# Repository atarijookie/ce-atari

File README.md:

# CosmosEx?
An ACSI/SCSI storage device connecting Raspberry Pi to the Atari 16/32 Bit range of computers
# What's what

ce_conf - Atari configuration client

ce_dd_bootsectors	- ACSI/SCSI boot sectors

ce_dd_prg	- driver for translated/network drives, date setting and screenshots

ce_fdd_prg	- Atari floppy emulator configuration client

ce_fdd_ttp	- Atari floppy emulator image mount helper

ce_franz_fw	- Firmware for floppy emulator

ce_hans_fw	- Firmware for harddisk emulator

ce_hdimg_ttp - Atari disk image mounter

ce_main_app	- Pi main app (translated/network drives, Webserver, HTTP Rest(like) API)

ce_mount_acc	- Atari unmount helper as ACC

ce_mount_prg	- Atari unmount helper

ce_screencast	- Atari screencast driver

cosmosex_downloader	- Atari ce_dd copier

cosmosex_fakesting	- Atari network driver (WIP)

cosmosex_onpc_pasti	- PC pasti.dll connection layer to PC compile ce_main_app

ffmpeg_build - build ffmpeg binary on RPi

flash_stm32	- Pi helper to flash STM32

flash_xilinx	- Pi helper to flash Xilinx

test_acsi	- Atari ACSI/SCSI transfer tester

test_filesystem	- Atari filesystem tester

test_floppy	- Atari floppy emulation tester

test_floppy_read	- Atari another floppy emulation tester

test_manual	- Atari another ACSI transfer tester

test_sting	- Atari STiNG tester

update - build the CosmosEx .zip update package

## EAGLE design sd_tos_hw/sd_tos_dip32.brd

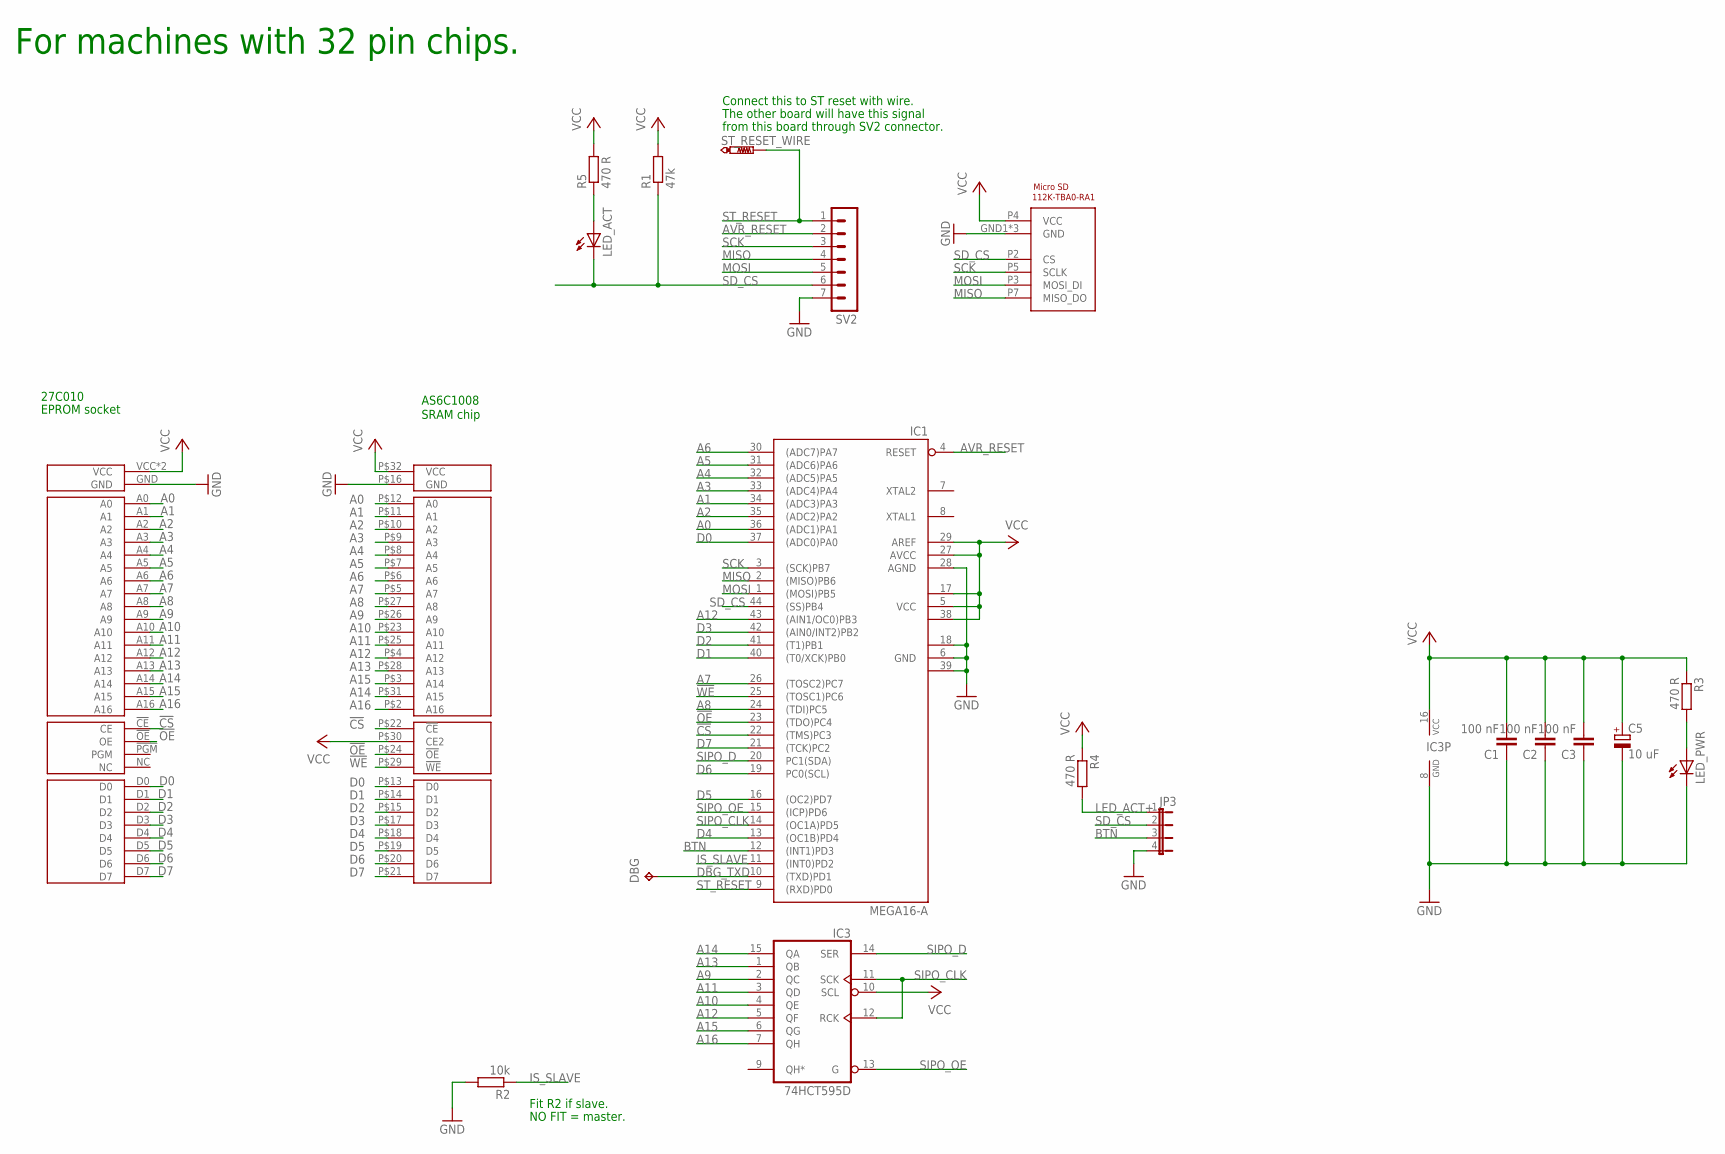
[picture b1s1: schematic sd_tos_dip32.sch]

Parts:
C1, C2, C3: 100 nF; C0603
C5: 10 uF; SANYO-OSCON_SMD_B6
DBG: TPB1,27; B1,27
IC1: MEGA16-A; TQFP44
IC3: 74HCT595D; SO16
JP3: JP4E; JP4
LED_ACT: LEDCHIP-LED0805; CHIP-LED0805
LED_PWR: LEDCHIP-LED0805; CHIP-LED0805
R1: 47k; R0603
R2: 10k; R0603
R3, R4, R5: 470 R; R0603
ST_RESET_WIRE: PTR1PAD1-13; P1-13
SV2: MA07-1
U$1: 27C010_BOTTOM_ONLY; DIP32_BOTTOM_ONLY
U$2: AS6C1008DIP32; DIP32
U$3: MICRO_SD

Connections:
!CS: IC1.22 ((TMS)PC3), U$1.!CE (CE), U$2.P$22 (!CE)
!OE: IC1.23 ((TDO)PC4), U$1.!OE (OE), U$2.P$24 (!OE)
!WE: IC1.25 ((TOSC1)PC6), U$2.P$29 (!WE)
A0: IC1.36 ((ADC1)PA1), U$1.A0, U$2.P$12 (A0)
A1: IC1.34 ((ADC3)PA3), U$1.A1, U$2.P$11 (A1)
A2: IC1.35 ((ADC2)PA2), U$1.A2, U$2.P$10 (A2)
A3: IC1.33 ((ADC4)PA4), U$1.A3, U$2.P$9 (A3)
A4: IC1.32 ((ADC5)PA5), U$1.A4, U$2.P$8 (A4)
A5: IC1.31 ((ADC6)PA6), U$1.A5, U$2.P$7 (A5)
A6: IC1.30 ((ADC7)PA7), U$1.A6, U$2.P$6 (A6)
A7: IC1.26 ((TOSC2)PC7), U$1.A7, U$2.P$5 (A7)
A8: IC1.24 ((TDI)PC5), U$1.A8, U$2.P$27 (A8)
A9: IC3.2 (QC), U$1.A9, U$2.P$26 (A9)
A10: IC3.4 (QE), U$1.A10, U$2.P$23 (A10)
A11: IC3.3 (QD), U$1.A11, U$2.P$25 (A11)
A12: IC1.43 ((AIN1/OC0)PB3), IC3.5 (QF), U$1.A12, U$2.P$4 (A12)
A13: IC3.1 (QB), U$1.A13, U$2.P$28 (A13)
A14: IC3.15 (QA), U$1.A14, U$2.P$31 (A15)
A15: IC3.6 (QG), U$1.A15, U$2.P$3 (A14)
A16: IC3.7 (QH), U$1.A16, U$2.P$2 (A16)
AVR_RESET: IC1.4 (RESET), SV2.2
BTN: IC1.12 ((INT1)PD3), JP3.3
D0: IC1.37 ((ADC0)PA0), U$1.D0, U$2.P$13 (D0)
D1: IC1.40 ((T0/XCK)PB0), U$1.D1, U$2.P$14 (D1)
D2: IC1.41 ((T1)PB1), U$1.D2, U$2.P$15 (D2)
D3: IC1.42 ((AIN0/INT2)PB2), U$1.D3, U$2.P$17 (D3)
D4: IC1.13 ((OC1B)PD4), U$1.D4, U$2.P$18 (D4)
D5: IC1.16 ((OC2)PD7), U$1.D5, U$2.P$19 (D5)
D6: IC1.19 (PC0(SCL)), U$1.D6, U$2.P$20 (D6)
D7: IC1.21 ((TCK)PC2), U$1.D7, U$2.P$21 (D7)
DBG_TXD: DBG.TP, IC1.10 ((TXD)PD1)
GND: C1.1, C2.1, C3.1, C5.-, IC1.6 (GND), IC1.18 (GND1), IC1.28 (AGND), IC1.39 (GND2), IC3.8 (GND), JP3.4, LED_PWR.C, R2.2, SV2.7, U$1.GND, U$2.P$16 (GND), U$3.GND1 (GND), U$3.GND2 (GND), U$3.P6 (GND)
IS_SLAVE: IC1.11 ((INT0)PD2), R2.1
LED_ACT+: JP3.1, R4.2
MISO: IC1.2 ((MISO)PB6), SV2.4, U$3.P7 (MISO_DO)
MOSI: IC1.1 ((MOSI)PB5), SV2.5, U$3.P3 (MOSI_DI)
unnamed: LED_PWR.A, R3.2
unnamed: LED_ACT.A, R5.1
SCK: IC1.3 ((SCK)PB7), SV2.3, U$3.P5 (SCLK)
SD_CS: IC1.44 ((SS)PB4), JP3.2, LED_ACT.C, R1.1, SV2.6, U$3.P2 (CS)
SIPO_CLK: IC1.14 ((OC1A)PD5), IC3.11 (SCK), IC3.12 (RCK)
SIPO_D: IC1.20 (PC1(SDA)), IC3.14 (SER)
SIPO_OE: IC1.15 ((ICP)PD6), IC3.13 (G)
ST_RESET: IC1.9 ((RXD)PD0), ST_RESET_WIRE.TP, SV2.1
VCC: C1.2, C2.2, C3.2, C5.+, IC1.5 (VCC), IC1.17 (VCC1), IC1.27 (AVCC), IC1.29 (AREF), IC1.38 (VCC2), IC3.10 (SCL), IC3.16 (VCC), R1.2, R3.1, R4.1, R5.2, U$1.VCC, U$1.VPP (VCC), U$2.P$30 (CE2), U$2.P$32 (VCC), U$3.P4 (VCC)

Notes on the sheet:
27C010
EPROM socket
SRAM chip
Fit R2 if slave.
NO FIT = master.
Connect this to ST reset with wire.
The other board will have this signal
from this board through SV2 connector.
AS6C1008
For machines with 32 pin chips.

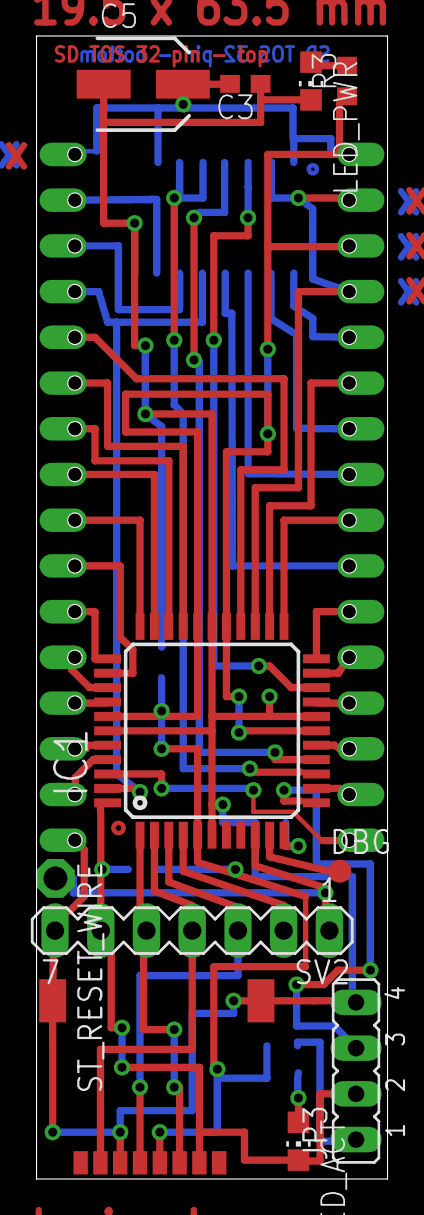
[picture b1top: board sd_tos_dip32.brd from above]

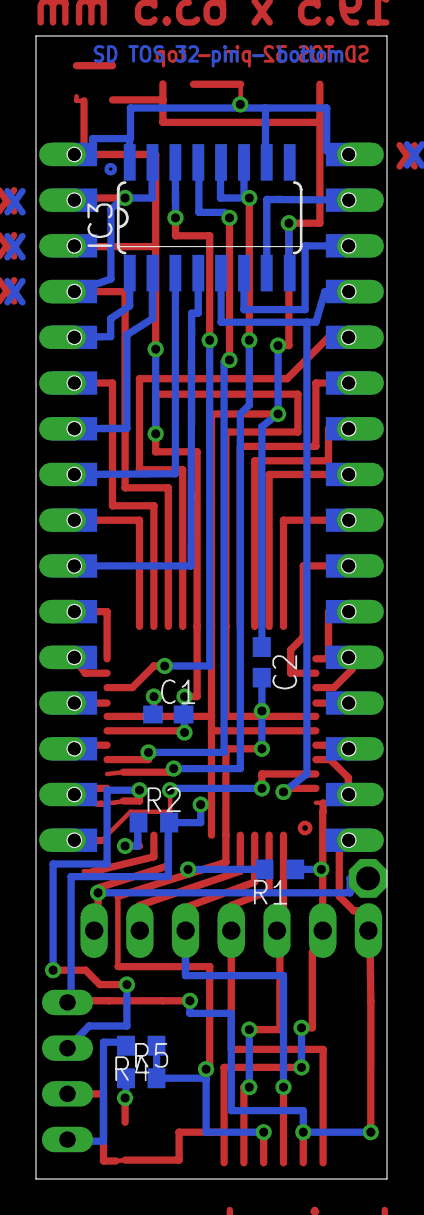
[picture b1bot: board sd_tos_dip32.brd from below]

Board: 2 copper layers, 19.5 x 63.5 mm, 20 parts (7 on the bottom side), 45 nets.

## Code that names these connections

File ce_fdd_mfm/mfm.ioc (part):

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Mcu.Name=STM32C011F(4-6)Px
Mcu.Package=TSSOP20
Mcu.UserName=STM32C011F4Px
PA0.Signal=S_TIM16_CH1
PA1.Mode=Full_Duplex_Slave
PA1.Signal=SPI1_SCK
PA13.Mode=Serial_Wire
PA13.Signal=DEBUG_SWDIO
PA14-BOOT0.Mode=Serial_Wire
PA14-BOOT0.Signal=DEBUG_SWCLK
PA2.Mode=Full_Duplex_Slave
PA2.Signal=SPI1_MOSI
PA3.Signal=GPIO_Input
PA4.Mode=NSS_Signal_Hard_Input
PA4.Signal=SPI1_NSS
PA5.Signal=GPIO_Output
PA6.Mode=Full_Duplex_Slave
PA6.Signal=SPI1_MISO
PB6.Signal=GPIO_Output
PB7.Signal=S_TIM3_CH1
RCC.HSE_VALUE=8000000
RCC.SYSCLKFreq_VALUE=48000000
board=custom

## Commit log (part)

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2022-12-16 handling client socket disconnect, fixed random kill of parent when child was terminated
2022-12-17 static web files added
2022-12-19 more fixes to missing files, versions, ...
2022-12-19 improvement on getting the terminal at least running somehow with appviasock
2022-12-20 added sketelons for web download and floppy interface
2022-12-22 floppy image upload to slot mostly done
2022-12-23 loading of shared settings from dotenv file
2022-12-23 dotenv usage added to ce_conf and ce_mounter
2022-12-23 few fixes on floppy image download
2022-12-26 downloading of floppy image lists moved from ce_fdd_py to task_queue
2022-12-27 added retrieving, showing and using image list in floppy image download via web
2022-12-29 getting and setting eth and wifi via nmcli, loading works, setting not tested
2022-12-30 fixed static and dhcp network setting
2023-01-01 network saving now in thread as it can take 15 seconds. Opening network screen during that now not allowed.
2023-01-02 loading and using dotEnv, some internal statuses now stored to file
2023-01-03 added dummy chipinterface and handling of floppy actions from core sock
2023-01-04 virtual mouse and keyboard should be working now again
2023-01-04 loading ce logo into initial screencast / screenshots shared memory
2023-01-05 triggering trans and raw disk reload from mounter
2023-01-07 added virtual symlink support to libdospath, with tests
2023-01-09 added support for browsable ZIPs again, not tested
2023-01-10 fixed app-via-sock opening and description via config stream
2023-01-14 fixes after running on raspbian
2023-01-17 venv dir now has hostname in it, so shared sources can have multiple venvs for multiple machines
2023-01-18 tweaks to ce status command
2023-01-23 fixed CE boot
2023-01-30 better conversion from VT100 to VT52
2023-02-01 fix for bad VT100 GOTO x,y command and clear screen after config app switch
2023-02-02 added mounted drives descriptions
2023-02-06 fuse-archive now used instead of fuse-zip, some fixes to zip mounting, still not perfect
2023-02-08 fix for waiting for zip mount, fix for zip-as-dir only on top level (no nested zip-dirs)
2023-02-10 added 'other settings' screen to config
2023-02-13 checking for python packages presence on apps start, then installing them (usefull for new packages after upgrade)
2023-02-14 fix for screencast colors in st high / mono
2023-02-17 check_for_update.sh now looks for update on mounted disks
2023-02-18 fix for bad settings restore
2023-02-21 changes due to services now being handled by systemd:
2023-02-22 fixes to starting scripts, permissions, update
2023-02-27 minor improvements, also storing software version after update
2023-03-15 added chip interface v3, which is just a copy of v1/v2
2023-03-20 more rewrite on chip interface v3
2023-03-21 added endian test and swapWord removed
2023-03-29 chip logs via uart
2023-04-04 improvements / fixes on chip interface v3
2023-04-17 display and ikbd sending
2023-05-23 removed license retrieval, disabled debug strings
2023-07-05 added tcp performance test client and server
2024-01-01 most of the chip interface v4 is implemented
2024-01-02 button handling, image slot handling
2024-01-06 button handling in Franz
2024-01-13 compiled on rpi, added some debug messages
2024-01-15 fix for failed reading
2024-01-26 read and write speed improvement
2024-02-12 this is the CE extension example written in python. Includes test with which the communication was verified.
2024-02-13 multiple fixes to CE extension handling, tested with extension_example
2024-02-15 function type and argument count added to signatures, better checking of function type
2024-02-17 added actual calling of extension via Fopen, also added the support for this call in CE_DD.PRG
2024-02-20 fixed the extension example for ST, fixed path translation of extension argument
2024-02-23 reoganizing main loop a little
2024-02-24 dotenv just sourced instead of using extra script to get the values
2024-03-01 IN_OE removed, extension example renamed
2024-03-03 fixes to Cpp extension example, seems to work now
2024-03-05 fix to power off and beeper
2024-03-22 skeleton for video-audio extension added
2024-03-23 retrieving audio and video frames from FIFOs
2024-03-26 starting and stopping of stream
2024-03-28 started to add playback code
2024-03-30 most of the video implementation done, starting audio implementation
2024-03-30 different frames and palette ordering, loging to file
2024-04-01 improvements to extension, starting to write test to fix extension not working
2024-04-11 multiple fixes to frames receiving, now seems to works, but still fails on repeated run
2024-04-23 adjustments to logs
2024-05-01 added brief hdd log, updated env on multiple places
2024-05-02 fixes to manual test
2024-05-08 longer timeout on SCSI commands, fixed timeout on ACSI
2024-05-09 more apps rely on libacsiscsi
2024-05-09 fakesting moved to libacsiscsi
2024-05-27 fixes to RaSCSI support, still not fully working, but much better now
2024-05-29 ncr 5380 register definitions renamed for clarity
2025-04-19 starting v4 by removing what will not be needed anymore
2025-04-20 removed flags that are not needed
2025-04-20 added separate hdd core
2025-04-21 hdd core simplified - removed code for ikbd, button, display, always starting as network server
2025-04-22 minor code changes, adjustments to network data receiving
2025-04-24 fixes to settings and configy
2025-04-25 removed support for mounting archives, added port to path of unix sockets, added simpler settings for RAW and TRANS drives
2025-04-26 added file selection to config page
2025-04-27 few settings and env vars renamed, webserver sends command to reload hdd settings to hdd core
2025-04-28 added ce ikdb uart resender
2025-04-30 minimal source taken from hans's firmware, made some adjustments, but not compiled, so full of errors
2025-05-01 minor code tweaks
2025-05-01 added settings reading, storing, connecting to wifi
2025-05-02 settings stored and read using preferences library, getting of incomming header added
2025-05-02 read and write simplified
2025-05-04 fixes to data transfers for the new esp network protocol
2025-05-05 fix for esp captive portal, fix for disconnects on core side
2025-05-06 added killing of core which doesn't report status
2025-05-06 disconnect based on last time data received
2025-05-10 removing things that won't be needed in CE lite
2025-05-10 symlinks fixed
2025-05-11 fixes to start script, added stop script
2025-05-13 fixes to not finding config drive and not loading settings
2025-05-23 hdd logs removed from core, data read / write with faster reg access, only one discovery packet type sent per second
2025-05-26 more logs and fix for timeout on write commands
2025-05-31 fix for bad reading
2025-05-31 dislay messages improved, now using hw i2c of esp32
2025-06-02 added ikbd core, compilable, but not tested
2025-06-02 fixed accept()ing connections and disconnecting on inactivity
2025-06-04 added alive marks from fw every 1 second
2025-06-10 added loading of log level from .env file
2025-06-19 added fw for stm32c011, which will handle mfm streaming
2025-06-21 mfm code reordering
2025-07-02 working on fdd core to make it compilable
2025-07-02 better handling of client fds and floppy slot indexes
2025-07-03 clients connected to their floppy slots
2025-07-03 added sending of whole track to device
2025-07-06 removed image factory, not saving floppy image paths in image silo, other simplifications
2025-07-06 more junk removed
2025-07-07 fdd core and fdd esp have now both the basic communication for sending track, iamge, written sectors
2025-07-09 fixes to ce_fdd_mfm to make spi and pwm work
2025-07-10 added code to handle mfm output stream, removed code not needed
2025-07-11 added start and end tag on written sector
2025-07-12 fixed sending and receiving of floppy image from server to esp32
2025-07-24 disk change implemented, fw report before requesting whole image
2025-07-27 using dma to do spi transfers in stm32
2025-07-28 mfm read now using dma, that solves the stream-breaking-issue
2025-07-29 written side, sector, track, storing and getting from buffer
2025-08-10 added storing and showing connected fdd clients
2025-08-10 path to file changed
2025-08-15 modified mostly comments
2025-08-22 improvements to fdd write
2025-08-27 fixes to fdd core, changes to fdd stream table
2025-08-27 removed commented out code
2025-09-05 reverted most of previous changes to write
2025-09-09 settings storing and loading to/from eeprom added
2025-09-11 added code for psram access, added mfm output config
2025-09-12 started to port pico fdd from arduino to VS Code
2025-09-14 settings via serial port
2025-09-15 changed to make writing to flash finally work
2025-09-16 for receiving of data client context was taken from existing library
2025-09-17 added i2c oled code
2025-09-21 connection related things in functions with connection as argument, now used in ikbd code
2025-09-24 added optional offset to manual test
2025-09-27 changes to make PSRAM work
2025-09-28 mfm streaming moved to core1, ikbd handling added to core0
2025-10-19 added PIO UART RX from example
2025-10-20 started using extra uart fifo
2025-10-23 bunch of files renamed
2025-11-01 reload of track into ram if just received the streamed track from network, track load and store protected by critical sections
2025-11-19 added modified ethernet library
2025-11-22 debug strings now send via debug() function
2025-11-22 added pio code for cmd + status transfers
2025-11-22 write pio changed, so that it won't do false INT / DRQ pulse
2025-11-22 started to use pio for acsi transfers, not complete yet
2025-11-24 improvements to PIO routines - reading 100 ns after CS / ACK falling edge, push at the end of routines
2025-11-27 changes and fixes to make the device connect and not hang
2025-11-29 fixes to pio read and write, also improvements in pio code
2025-11-29 timeout code added back for pico
2025-12-02 fix for data and status not being read
2025-12-06 fixed i2c display init on pico hdd
2025-12-10 started scsi pico project, based on acsi pico
2025-12-10 fix for scsi handshake
2025-12-22 debug via uart on LED pin
2025-12-24 uart debug wrapped in ifdefs
2025-12-25 ce_pico_hdd renamed ce_pico_hdd_acsi
2025-12-30 fix to scsi selection not working
2026-01-03 fix for dma_read failing due to c&p of scsi_write_program_init where read init should be
2026-01-04 fix for scsi selection ignoring some requests
2026-01-08 replaced OLED display with 7 segment display
2026-01-09 fix for display writing
2026-01-12 hdd code moved into hdd dir
2026-01-14 added discovery service to this code
2026-01-15 minor defs cleanup
2026-01-19 fixes to display before connect
2026-01-19 added boiler plate for webserver in go
2026-01-19 added getting device list and following to page for specific device
2026-01-19 made hdd config working
2026-01-20 added handling of floppy endpoints and floppy page. added sending commands via socket
2026-01-20 centering of html pages
2026-01-20 mostly visual improvements on the web pages - better look, footer, logout button
2026-01-20 removed python webserver, renamed go webserver
2026-01-21 settings use prefix as folder now
2026-01-23 ikbd uses just single settings, not by mac
2026-01-24 hdd, fdd, ikbd fix for listening ports, webserver creating pid file, removed franz, hans, mfm firmwares
2026-01-26 added storing and using device mac right after connect
2026-01-27 fixed settings by removing trailing underscore, added link to screencast in web, not showing device with all zeros in web, removed junk code from go webserver part
2026-01-27 minor ikbd changes
2026-01-28 fix for crash on acsi settings change / raw disk reload
2026-01-28 file selector on acsi_ids and gem_drives now back to center, screencast now receiving images
2026-02-05 some logging in cores
2026-02-09 loading track by sectors
2026-02-10 index pulse handling in core1 next to streaming
2026-02-16 fix for writing/reading from wrong queue
2026-02-17 core1 loading and storing to psram, data passed via queue
